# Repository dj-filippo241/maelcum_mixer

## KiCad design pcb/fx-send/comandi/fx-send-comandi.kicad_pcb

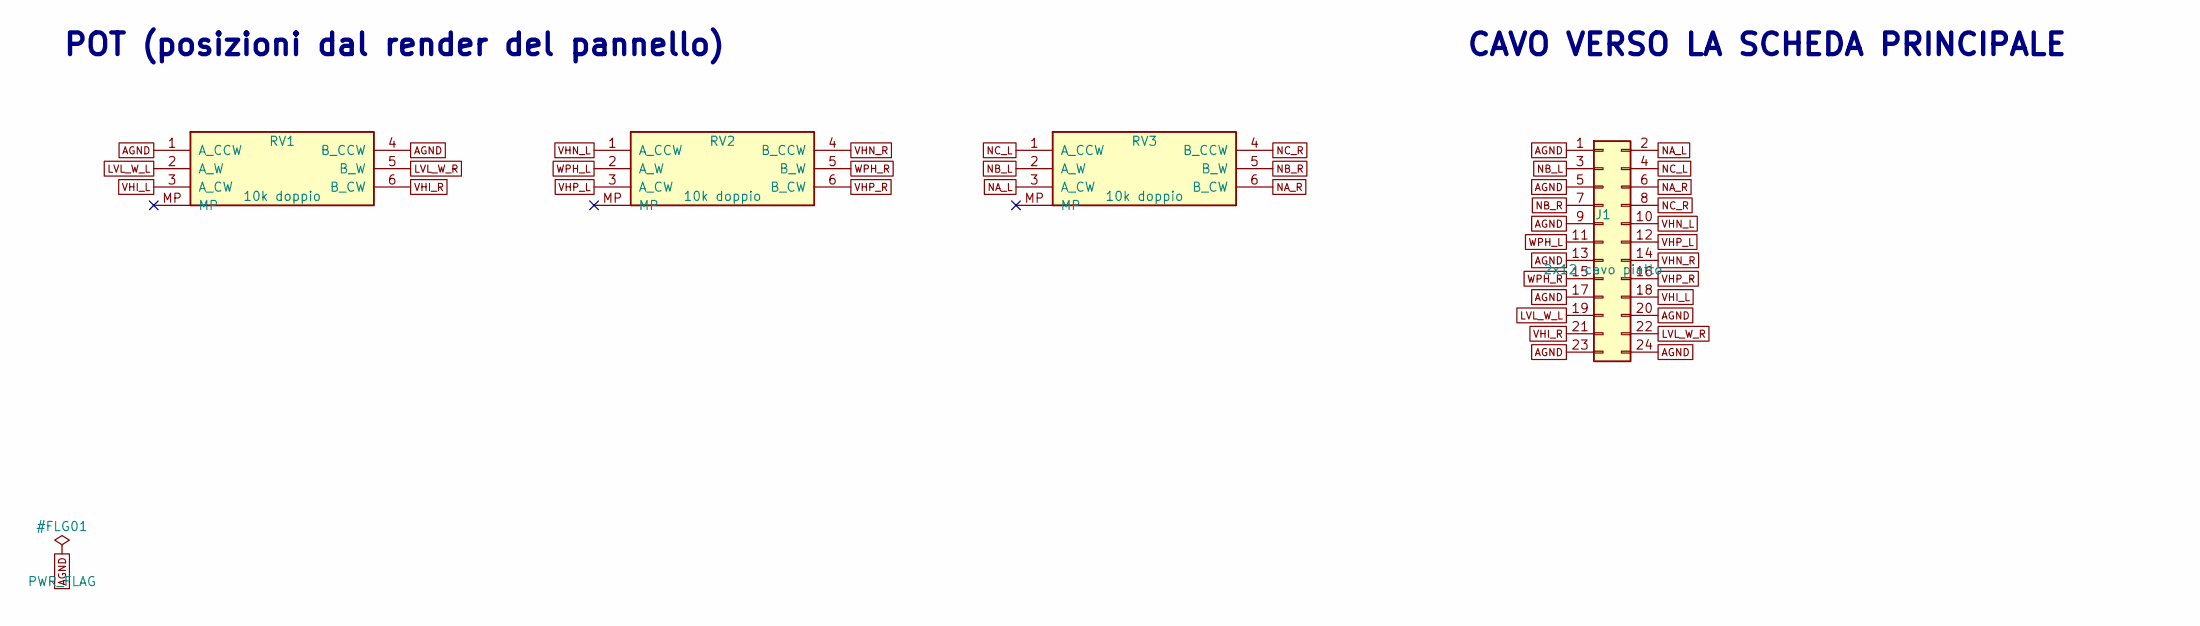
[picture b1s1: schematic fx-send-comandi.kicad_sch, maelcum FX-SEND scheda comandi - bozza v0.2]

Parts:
J1: 2x12 cavo piatto; PinHeader_2x12_P2.54mm_Vertical
RV1, RV2, RV3: 10k doppio; Potentiometer_Alps_RK09L_Double_Vertical

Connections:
AGND: J1.1, J1.5, J1.9, J1.13, J1.17, J1.20, J1.23, J1.24, RV1.1 (A_CCW), RV1.4 (B_CCW)
LVL_W_L: J1.19, RV1.2 (A_W)
LVL_W_R: J1.22, RV1.5 (B_W)
NA_L: J1.2, RV3.3 (A_CW)
NA_R: J1.6, RV3.6 (B_CW)
NB_L: J1.3, RV3.2 (A_W)
NB_R: J1.7, RV3.5 (B_W)
NC_L: J1.4, RV3.1 (A_CCW)
NC_R: J1.8, RV3.4 (B_CCW)
VHI_L: J1.18, RV1.3 (A_CW)
VHI_R: J1.21, RV1.6 (B_CW)
VHN_L: J1.10, RV2.1 (A_CCW)
VHN_R: J1.14, RV2.4 (B_CCW)
VHP_L: J1.12, RV2.3 (A_CW)
VHP_R: J1.16, RV2.6 (B_CW)
WPH_L: J1.11, RV2.2 (A_W)
WPH_R: J1.15, RV2.5 (B_W)

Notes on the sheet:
POT (posizioni dal render del pannello)
CAVO VERSO LA SCHEDA PRINCIPALE

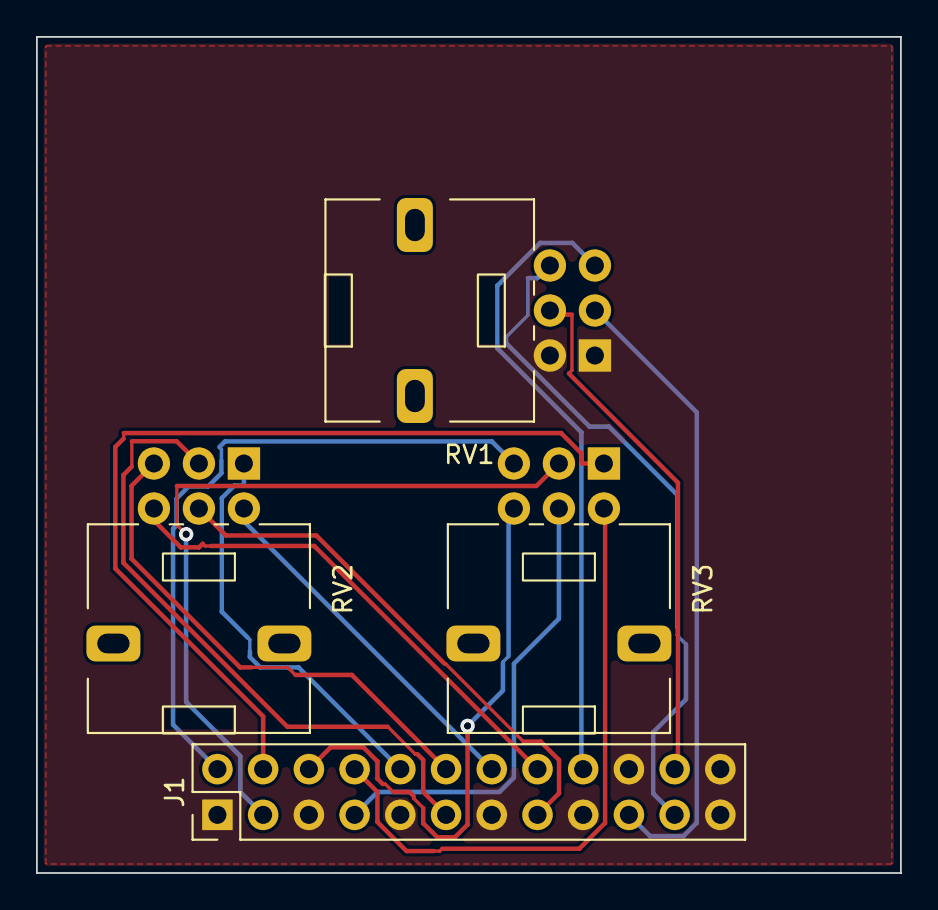
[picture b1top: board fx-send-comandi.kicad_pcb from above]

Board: 4 copper layers, 48.0 x 46.5 mm, 4 parts (0 on the bottom side), 17 nets.

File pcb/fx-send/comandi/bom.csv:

quantita;valore;impronta;riferimenti;nota
1;2x12 cavo piatto;PinHeader_2x12_P2.54mm_Vertical;J1;stesso ordine di J2 su fx-send.py
1;10k doppio;Potentiometer_Alps_RK09L_Double_Vertical;RV1;LEVEL: tutto antiorario = silenzio; manopola LEVEL, cappuccio 12.0 mm
1;10k doppio;Potentiometer_Alps_RK09L_Double_Vertical;RV2;HIGH: tutto antiorario = kill (Rp1h = 0, fx-eq2.cir); manopola EQ HIGH, cappuccio 6.0 mm
1;10k doppio;Potentiometer_Alps_RK09L_Double_Vertical;RV3;LOW Baxandall: tutto antiorario = kill (Za max), cursore = massa virtuale; manopola EQ LOW, cappuccio 6.0 mm

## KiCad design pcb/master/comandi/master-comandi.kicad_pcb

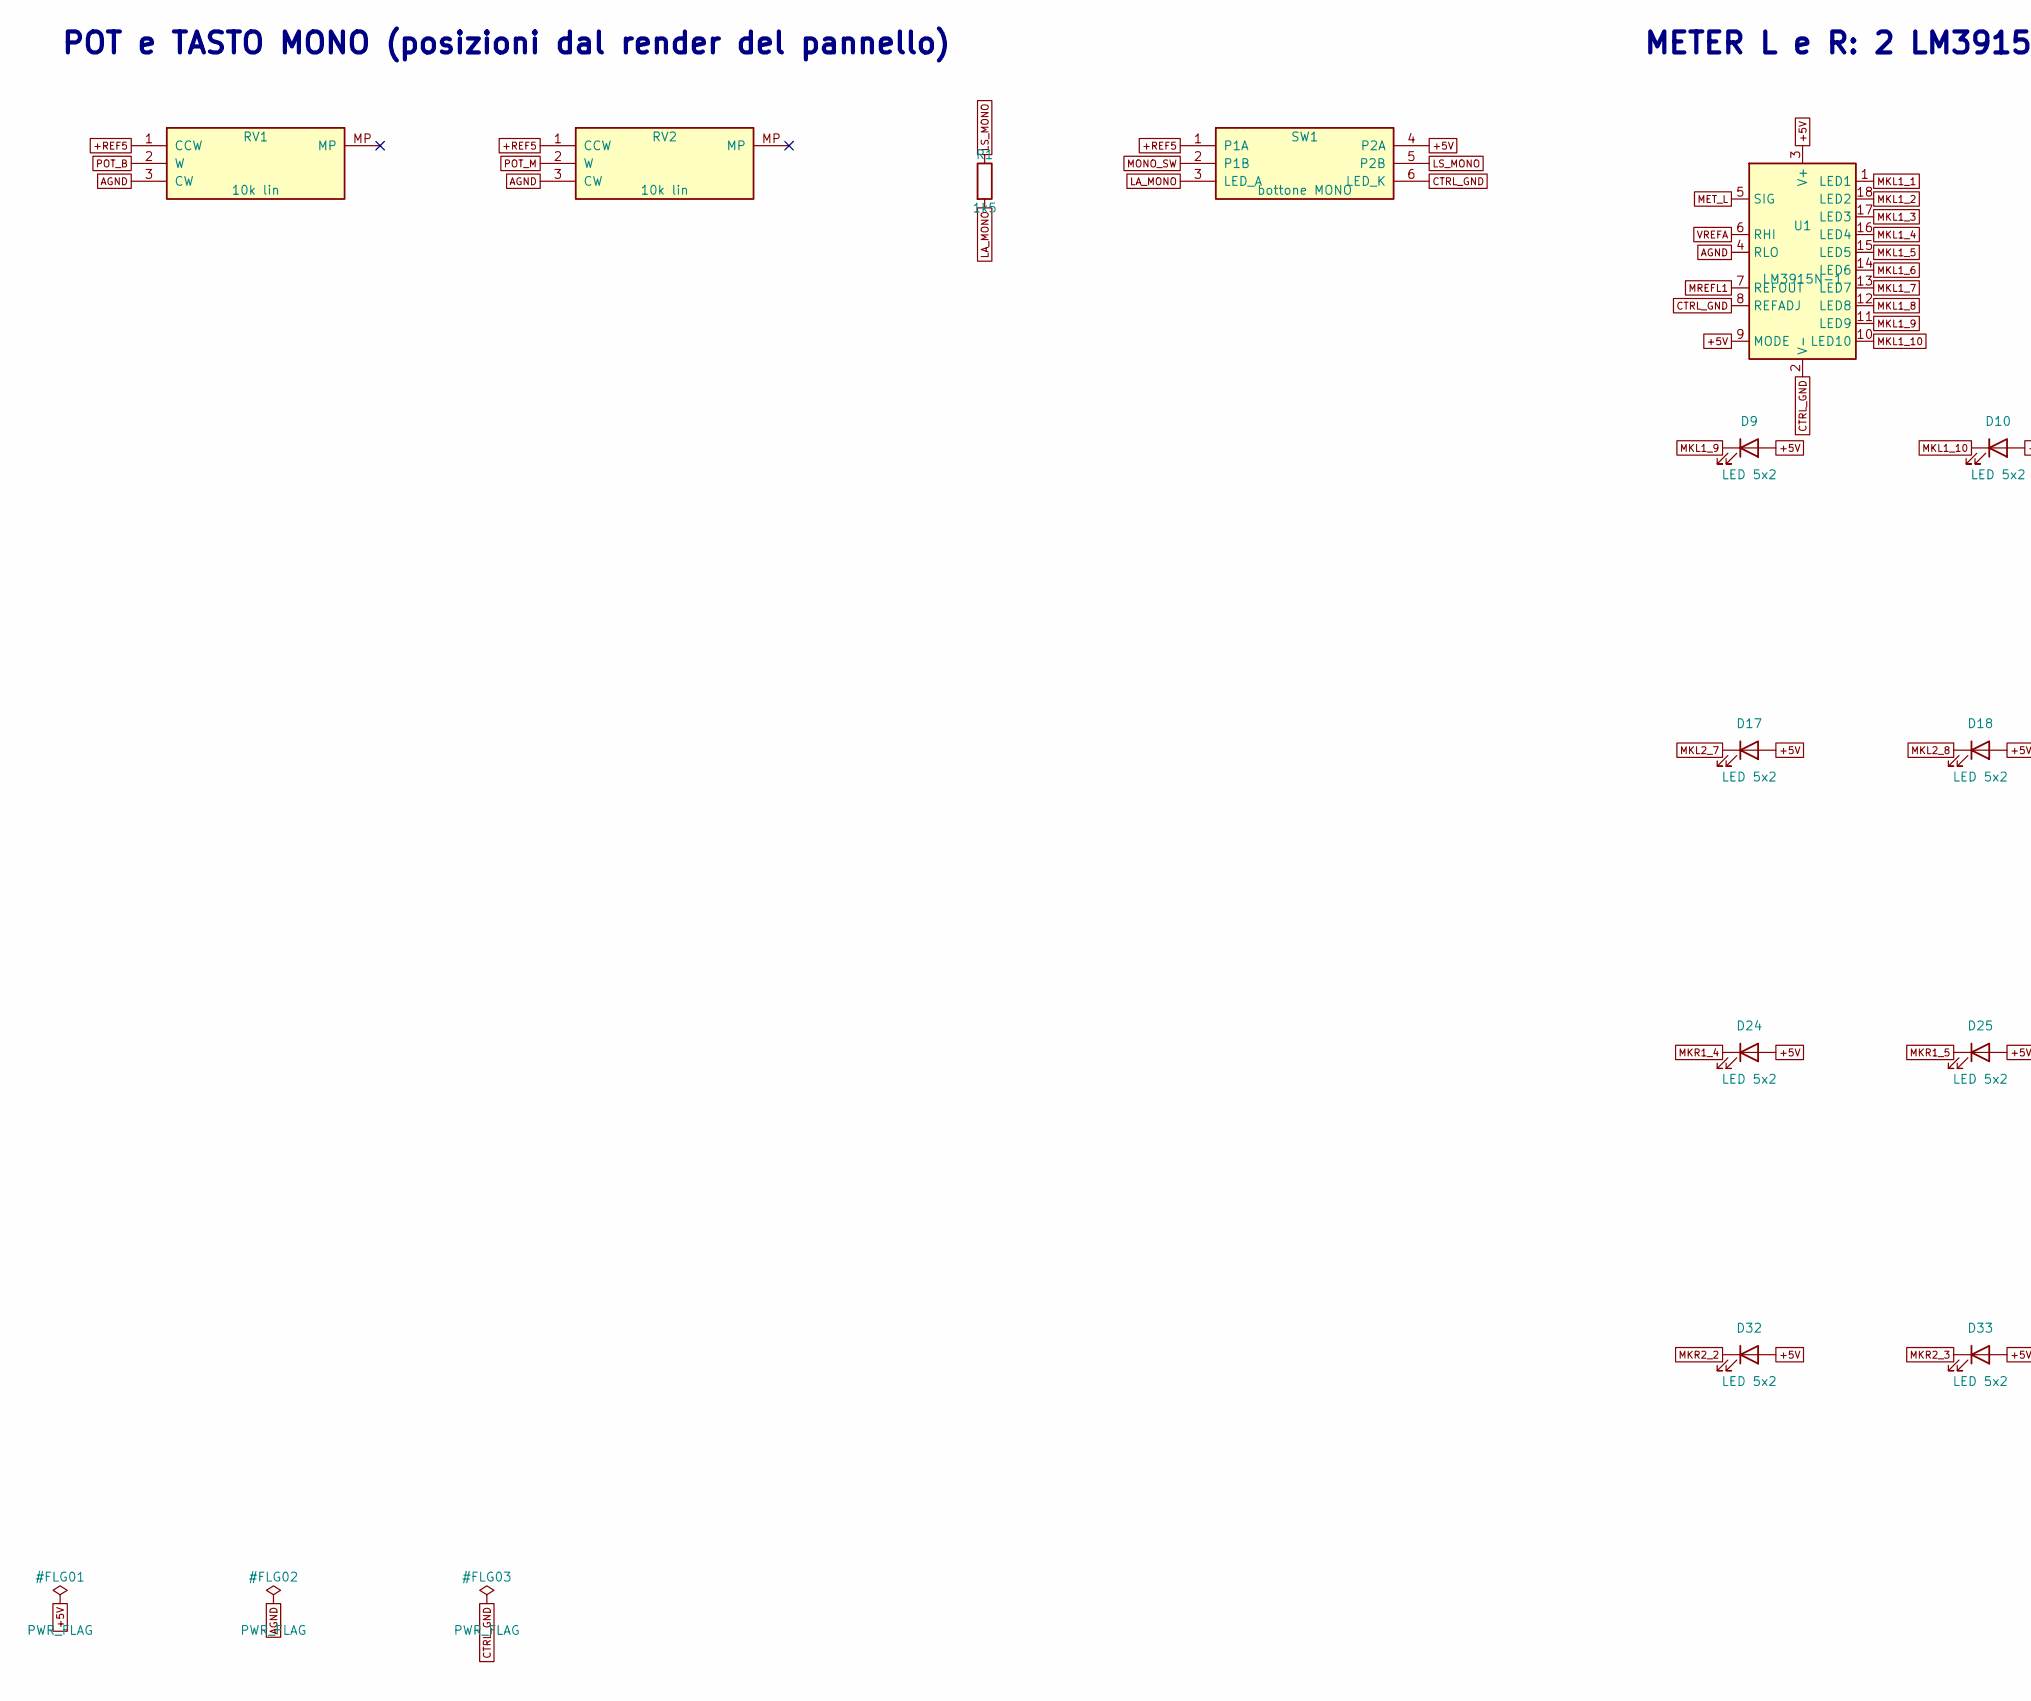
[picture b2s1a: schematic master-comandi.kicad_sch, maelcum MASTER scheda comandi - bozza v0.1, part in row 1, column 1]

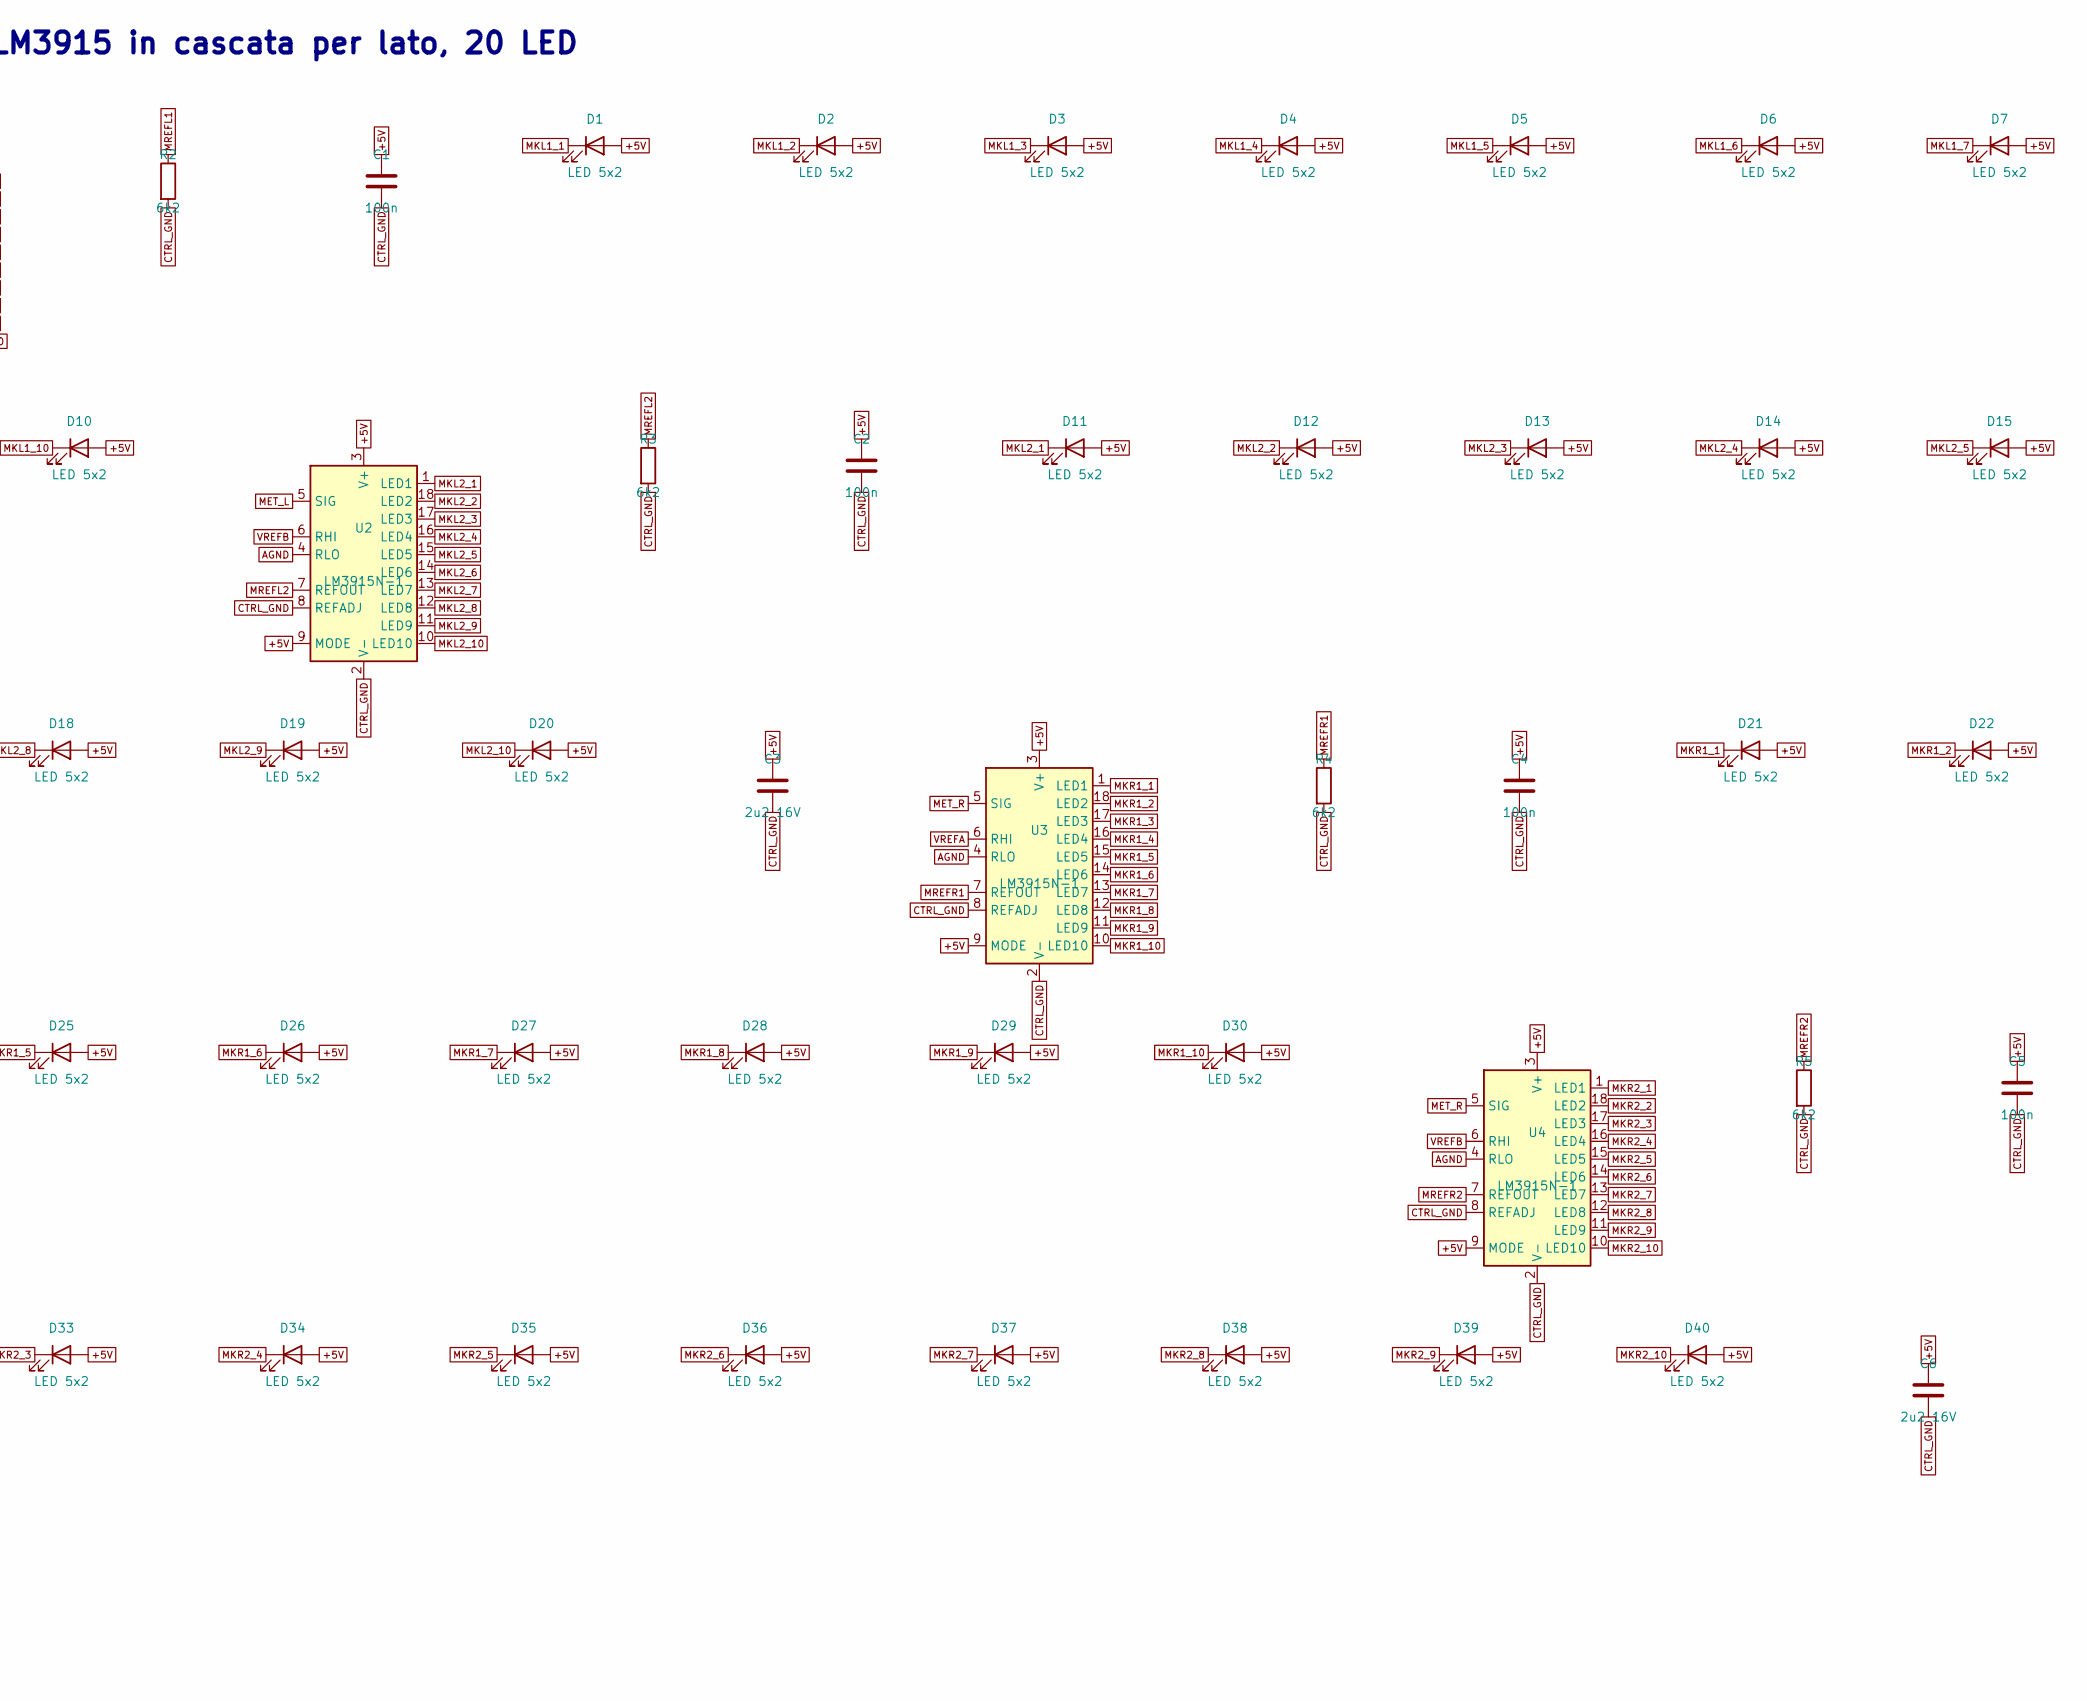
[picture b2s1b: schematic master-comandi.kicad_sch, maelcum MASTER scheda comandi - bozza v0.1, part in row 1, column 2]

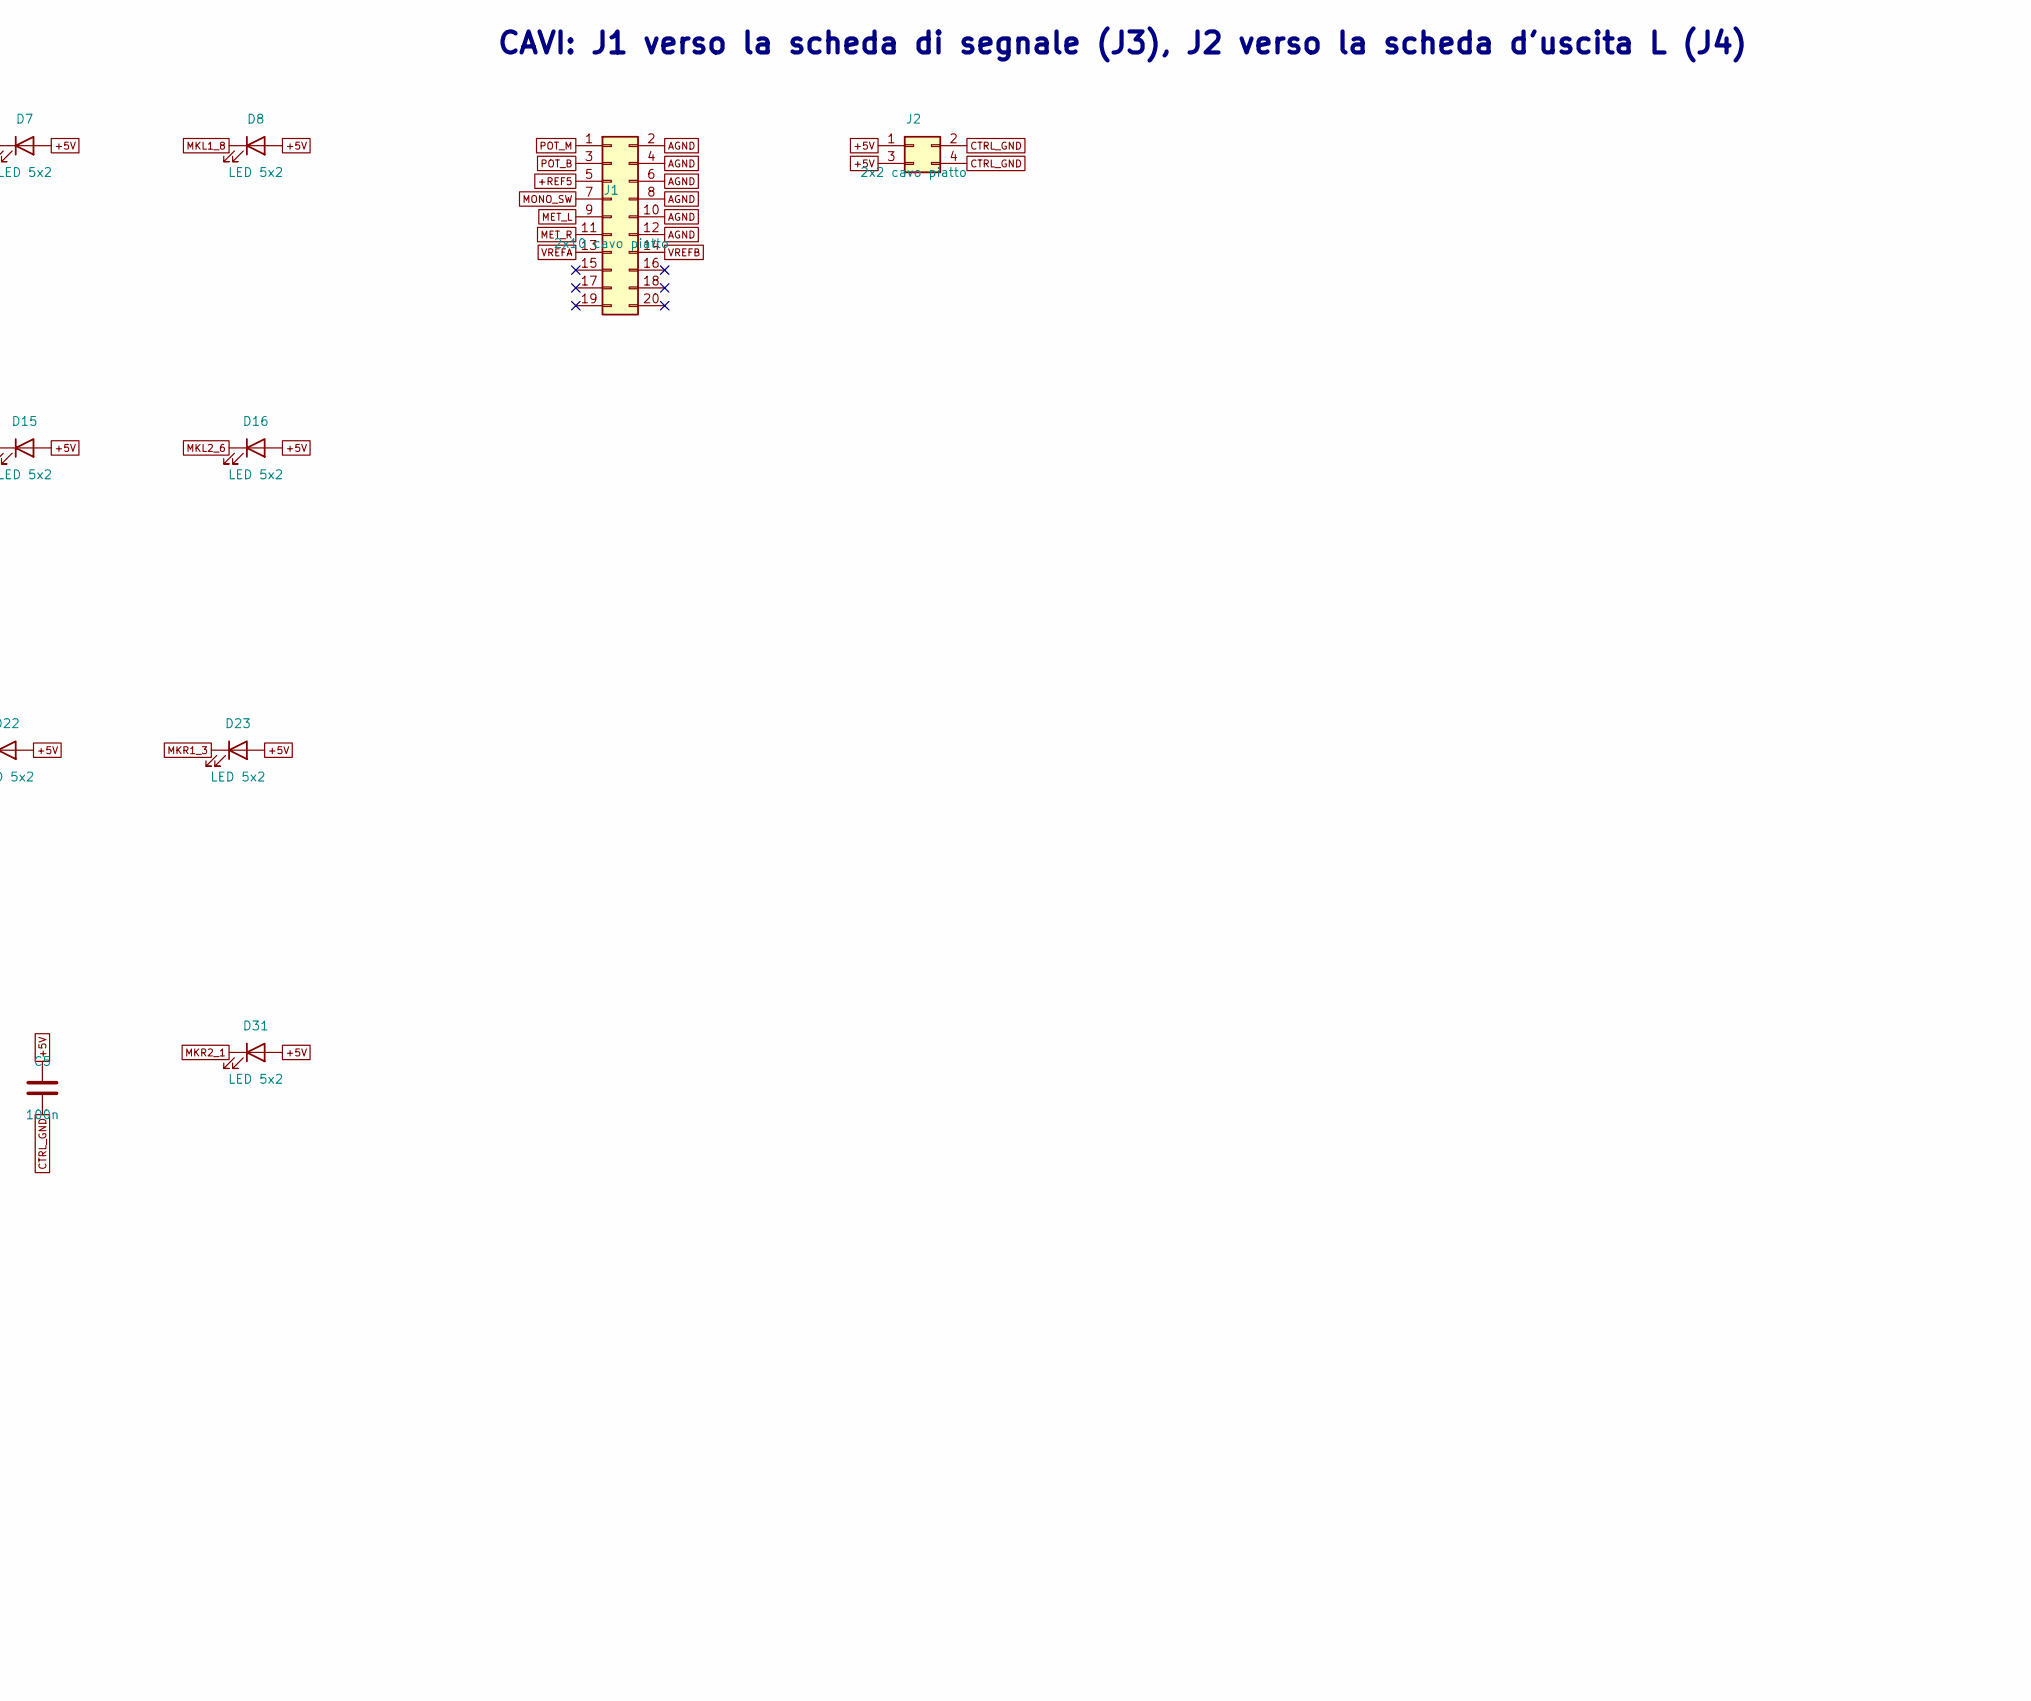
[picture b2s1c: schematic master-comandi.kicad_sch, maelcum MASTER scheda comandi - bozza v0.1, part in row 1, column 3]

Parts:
C1, C2, C4, C5: 100n; C_0805_2012Metric
C3, C6: 2u2 16V; C_1206_3216Metric
D1, D2, D3, D4, D5, D6, D7, D8, D9, D10, D11, D12, D13, D14, D15, D16, D17, D18, D19, D20, D21, D22, D23, D24, D25, D26, D27, D28, D29, D30, D31, D32, D33, D34, D35, D36, D37, D38, D39, D40: LED 5x2; LED_Rectangular_W5.0mm_H2.0mm
J1: 2x10 cavo piatto; PinHeader_2x10_P2.54mm_Vertical
J2: 2x2 cavo piatto; PinHeader_2x02_P2.54mm_Vertical
R1: 1k5; R_0805_2012Metric
R2, R3, R4, R5: 6k2; R_0805_2012Metric
RV1, RV2: 10k lin; Potentiometer_Alps_RK09L_Single_Vertical
SW1: bottone MONO; SW_NKK_GW12LJP
U1, U2, U3, U4: LM3915N-1; DIP-18_W7.62mm

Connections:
+5V: C1.1, C2.1, C3.1, C4.1, C5.1, C6.1, D1.2 (A), D2.2 (A), D3.2 (A), D4.2 (A), D5.2 (A), D6.2 (A), D7.2 (A), D8.2 (A), D9.2 (A), D10.2 (A), D11.2 (A), D12.2 (A), D13.2 (A), D14.2 (A), D15.2 (A), D16.2 (A), D17.2 (A), D18.2 (A), D19.2 (A), D20.2 (A), D21.2 (A), D22.2 (A), D23.2 (A), D24.2 (A), D25.2 (A), D26.2 (A), D27.2 (A), D28.2 (A), D29.2 (A), D30.2 (A), D31.2 (A), D32.2 (A), D33.2 (A), D34.2 (A), D35.2 (A), D36.2 (A), D37.2 (A), D38.2 (A), D39.2 (A), D40.2 (A), J2.1, J2.3, SW1.4 (P2A), U1.3 (V+), U1.9 (MODE), U2.3 (V+), U2.9 (MODE), U3.3 (V+), U3.9 (MODE), U4.3 (V+), U4.9 (MODE)
+REF5: J1.5, RV1.1 (CCW), RV2.1 (CCW), SW1.1 (P1A)
AGND: J1.2, J1.4, J1.6, J1.8, J1.10, J1.12, RV1.3 (CW), RV2.3 (CW), U1.4 (RLO), U2.4 (RLO), U3.4 (RLO), U4.4 (RLO)
CTRL_GND: C1.2, C2.2, C3.2, C4.2, C5.2, C6.2, J2.2, J2.4, R2.2, R3.2, R4.2, R5.2, SW1.6 (LED_K), U1.2 (V-), U1.8 (REFADJ), U2.2 (V-), U2.8 (REFADJ), U3.2 (V-), U3.8 (REFADJ), U4.2 (V-), U4.8 (REFADJ)
LA_MONO: R1.2, SW1.3 (LED_A)
LS_MONO: R1.1, SW1.5 (P2B)
MET_L: J1.9, U1.5 (SIG), U2.5 (SIG)
MET_R: J1.11, U3.5 (SIG), U4.5 (SIG)
MKL1_1: D1.1 (K), U1.1 (LED1)
MKL1_2: D2.1 (K), U1.18 (LED2)
MKL1_3: D3.1 (K), U1.17 (LED3)
MKL1_4: D4.1 (K), U1.16 (LED4)
MKL1_5: D5.1 (K), U1.15 (LED5)
MKL1_6: D6.1 (K), U1.14 (LED6)
MKL1_7: D7.1 (K), U1.13 (LED7)
MKL1_8: D8.1 (K), U1.12 (LED8)
MKL1_9: D9.1 (K), U1.11 (LED9)
MKL1_10: D10.1 (K), U1.10 (LED10)
MKL2_1: D11.1 (K), U2.1 (LED1)
MKL2_2: D12.1 (K), U2.18 (LED2)
MKL2_3: D13.1 (K), U2.17 (LED3)
MKL2_4: D14.1 (K), U2.16 (LED4)
MKL2_5: D15.1 (K), U2.15 (LED5)
MKL2_6: D16.1 (K), U2.14 (LED6)
MKL2_7: D17.1 (K), U2.13 (LED7)
MKL2_8: D18.1 (K), U2.12 (LED8)
MKL2_9: D19.1 (K), U2.11 (LED9)
MKL2_10: D20.1 (K), U2.10 (LED10)
MKR1_1: D21.1 (K), U3.1 (LED1)
MKR1_2: D22.1 (K), U3.18 (LED2)
MKR1_3: D23.1 (K), U3.17 (LED3)
MKR1_4: D24.1 (K), U3.16 (LED4)
MKR1_5: D25.1 (K), U3.15 (LED5)
MKR1_6: D26.1 (K), U3.14 (LED6)
MKR1_7: D27.1 (K), U3.13 (LED7)
MKR1_8: D28.1 (K), U3.12 (LED8)
MKR1_9: D29.1 (K), U3.11 (LED9)
MKR1_10: D30.1 (K), U3.10 (LED10)
MKR2_1: D31.1 (K), U4.1 (LED1)
MKR2_2: D32.1 (K), U4.18 (LED2)
MKR2_3: D33.1 (K), U4.17 (LED3)
MKR2_4: D34.1 (K), U4.16 (LED4)
MKR2_5: D35.1 (K), U4.15 (LED5)
MKR2_6: D36.1 (K), U4.14 (LED6)
MKR2_7: D37.1 (K), U4.13 (LED7)
MKR2_8: D38.1 (K), U4.12 (LED8)
MKR2_9: D39.1 (K), U4.11 (LED9)
MKR2_10: D40.1 (K), U4.10 (LED10)
MONO_SW: J1.7, SW1.2 (P1B)
MREFL1: R2.1, U1.7 (REFOUT)
MREFL2: R3.1, U2.7 (REFOUT)
MREFR1: R4.1, U3.7 (REFOUT)
MREFR2: R5.1, U4.7 (REFOUT)
POT_B: J1.3, RV1.2 (W)
POT_M: J1.1, RV2.2 (W)
VREFA: J1.13, U1.6 (RHI), U3.6 (RHI)
VREFB: J1.14, U2.6 (RHI), U4.6 (RHI)

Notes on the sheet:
POT e TASTO MONO (posizioni dal render del pannello)
METER L e R: 2 LM3915 in cascata per lato, 20 LED
CAVI: J1 verso la scheda di segnale (J3), J2 verso la scheda d'uscita L (J4)

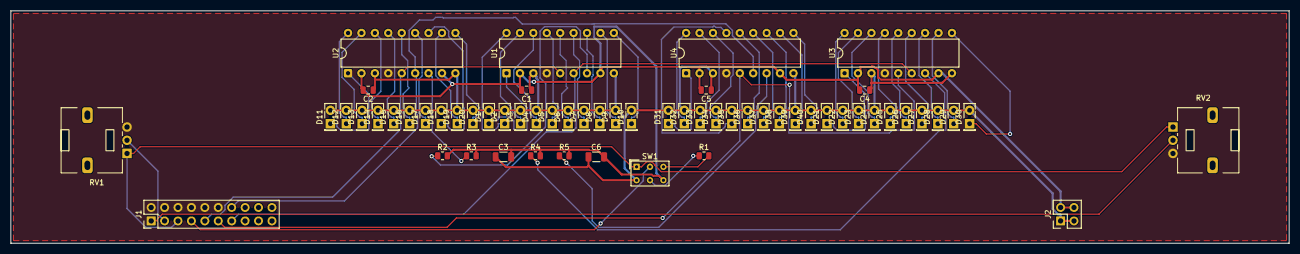
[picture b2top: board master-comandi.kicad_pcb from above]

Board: 4 copper layers, 242.0 x 44.0 mm, 60 parts (0 on the bottom side), 57 nets.

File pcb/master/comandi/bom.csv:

quantita;valore;impronta;riferimenti;nota
1;100n;C_0805_2012Metric;C1;disaccoppiamento dell'LM3915 L1
1;100n;C_0805_2012Metric;C2;disaccoppiamento dell'LM3915 L2
2;2u2 16V;C_1206_3216Metric;C3 C6;NOTA: riserva locale dei LED (cavo lungo)
1;100n;C_0805_2012Metric;C4;disaccoppiamento dell'LM3915 R1
1;100n;C_0805_2012Metric;C5;disaccoppiamento dell'LM3915 R2
1;LED 5x2;LED_Rectangular_W5.0mm_H2.0mm;D1;barra L, segmento 11 di 20 (1 = soglia più bassa); colore: metering §3
1;LED 5x2;LED_Rectangular_W5.0mm_H2.0mm;D10;barra L, segmento 20 di 20 (1 = soglia più bassa); colore: metering §3
1;LED 5x2;LED_Rectangular_W5.0mm_H2.0mm;D11;barra L, segmento 1 di 20 (1 = soglia più bassa); colore: metering §3
1;LED 5x2;LED_Rectangular_W5.0mm_H2.0mm;D12;barra L, segmento 2 di 20 (1 = soglia più bassa); colore: metering §3
1;LED 5x2;LED_Rectangular_W5.0mm_H2.0mm;D13;barra L, segmento 3 di 20 (1 = soglia più bassa); colore: metering §3
1;LED 5x2;LED_Rectangular_W5.0mm_H2.0mm;D14;barra L, segmento 4 di 20 (1 = soglia più bassa); colore: metering §3
1;LED 5x2;LED_Rectangular_W5.0mm_H2.0mm;D15;barra L, segmento 5 di 20 (1 = soglia più bassa); colore: metering §3
1;LED 5x2;LED_Rectangular_W5.0mm_H2.0mm;D16;barra L, segmento 6 di 20 (1 = soglia più bassa); colore: metering §3
1;LED 5x2;LED_Rectangular_W5.0mm_H2.0mm;D17;barra L, segmento 7 di 20 (1 = soglia più bassa); colore: metering §3
1;LED 5x2;LED_Rectangular_W5.0mm_H2.0mm;D18;barra L, segmento 8 di 20 (1 = soglia più bassa); colore: metering §3
1;LED 5x2;LED_Rectangular_W5.0mm_H2.0mm;D19;barra L, segmento 9 di 20 (1 = soglia più bassa); colore: metering §3
1;LED 5x2;LED_Rectangular_W5.0mm_H2.0mm;D2;barra L, segmento 12 di 20 (1 = soglia più bassa); colore: metering §3
1;LED 5x2;LED_Rectangular_W5.0mm_H2.0mm;D20;barra L, segmento 10 di 20 (1 = soglia più bassa); colore: metering §3
1;LED 5x2;LED_Rectangular_W5.0mm_H2.0mm;D21;barra R, segmento 11 di 20 (1 = soglia più bassa); colore: metering §3
1;LED 5x2;LED_Rectangular_W5.0mm_H2.0mm;D22;barra R, segmento 12 di 20 (1 = soglia più bassa); colore: metering §3
1;LED 5x2;LED_Rectangular_W5.0mm_H2.0mm;D23;barra R, segmento 13 di 20 (1 = soglia più bassa); colore: metering §3
1;LED 5x2;LED_Rectangular_W5.0mm_H2.0mm;D24;barra R, segmento 14 di 20 (1 = soglia più bassa); colore: metering §3
1;LED 5x2;LED_Rectangular_W5.0mm_H2.0mm;D25;barra R, segmento 15 di 20 (1 = soglia più bassa); colore: metering §3
1;LED 5x2;LED_Rectangular_W5.0mm_H2.0mm;D26;barra R, segmento 16 di 20 (1 = soglia più bassa); colore: metering §3
1;LED 5x2;LED_Rectangular_W5.0mm_H2.0mm;D27;barra R, segmento 17 di 20 (1 = soglia più bassa); colore: metering §3
1;LED 5x2;LED_Rectangular_W5.0mm_H2.0mm;D28;barra R, segmento 18 di 20 (1 = soglia più bassa); colore: metering §3
1;LED 5x2;LED_Rectangular_W5.0mm_H2.0mm;D29;barra R, segmento 19 di 20 (1 = soglia più bassa); colore: metering §3
1;LED 5x2;LED_Rectangular_W5.0mm_H2.0mm;D3;barra L, segmento 13 di 20 (1 = soglia più bassa); colore: metering §3
1;LED 5x2;LED_Rectangular_W5.0mm_H2.0mm;D30;barra R, segmento 20 di 20 (1 = soglia più bassa); colore: metering §3
1;LED 5x2;LED_Rectangular_W5.0mm_H2.0mm;D31;barra R, segmento 1 di 20 (1 = soglia più bassa); colore: metering §3
1;LED 5x2;LED_Rectangular_W5.0mm_H2.0mm;D32;barra R, segmento 2 di 20 (1 = soglia più bassa); colore: metering §3
1;LED 5x2;LED_Rectangular_W5.0mm_H2.0mm;D33;barra R, segmento 3 di 20 (1 = soglia più bassa); colore: metering §3
1;LED 5x2;LED_Rectangular_W5.0mm_H2.0mm;D34;barra R, segmento 4 di 20 (1 = soglia più bassa); colore: metering §3
1;LED 5x2;LED_Rectangular_W5.0mm_H2.0mm;D35;barra R, segmento 5 di 20 (1 = soglia più bassa); colore: metering §3
1;LED 5x2;LED_Rectangular_W5.0mm_H2.0mm;D36;barra R, segmento 6 di 20 (1 = soglia più bassa); colore: metering §3
1;LED 5x2;LED_Rectangular_W5.0mm_H2.0mm;D37;barra R, segmento 7 di 20 (1 = soglia più bassa); colore: metering §3
1;LED 5x2;LED_Rectangular_W5.0mm_H2.0mm;D38;barra R, segmento 8 di 20 (1 = soglia più bassa); colore: metering §3
1;LED 5x2;LED_Rectangular_W5.0mm_H2.0mm;D39;barra R, segmento 9 di 20 (1 = soglia più bassa); colore: metering §3
1;LED 5x2;LED_Rectangular_W5.0mm_H2.0mm;D4;barra L, segmento 14 di 20 (1 = soglia più bassa); colore: metering §3
1;LED 5x2;LED_Rectangular_W5.0mm_H2.0mm;D40;barra R, segmento 10 di 20 (1 = soglia più bassa); colore: metering §3
1;LED 5x2;LED_Rectangular_W5.0mm_H2.0mm;D5;barra L, segmento 15 di 20 (1 = soglia più bassa); colore: metering §3
1;LED 5x2;LED_Rectangular_W5.0mm_H2.0mm;D6;barra L, segmento 16 di 20 (1 = soglia più bassa); colore: metering §3
1;LED 5x2;LED_Rectangular_W5.0mm_H2.0mm;D7;barra L, segmento 17 di 20 (1 = soglia più bassa); colore: metering §3
1;LED 5x2;LED_Rectangular_W5.0mm_H2.0mm;D8;barra L, segmento 18 di 20 (1 = soglia più bassa); colore: metering §3
1;LED 5x2;LED_Rectangular_W5.0mm_H2.0mm;D9;barra L, segmento 19 di 20 (1 = soglia più bassa); colore: metering §3
1;2x10 cavo piatto;PinHeader_2x10_P2.54mm_Vertical;J1;stesso ordine di J3 su master-segnale.py; CLIP_L e CLIP_R liberi (nessun LED di clip sul pannello)
1;2x2 cavo piatto;PinHeader_2x02_P2.54mm_Vertical;J2;stesso ordine di J4 su master-uscita.py L: pin alternati (pcb/master/NOTE.md)
1;1k5;R_0805_2012Metric;R1;luce del bottone MONO dal secondo contatto
4;6k2;R_0805_2012Metric;R2 R3 R4 R5;NOTA: corrente dei LED ~2 mA (metering §1): I = 12,5 V / R, formula del datasheet LM3915 da verificare
1;10k lin;Potentiometer_Alps_RK09L_Single_Vertical;RV1;BOOTH: antiorario = silenzio; manopola rovescia: antiorario = +REF5; manopola BOOTH, pot di classe 14 mm, cappuccio 15.0 mm
1;10k lin;Potentiometer_Alps_RK09L_Single_Vertical;RV2;MASTER: antiorario = silenzio, scatto al centro = 0 dB, orario = +6 dB; manopola rovescia: antiorario = +REF5; manopola MASTER, pot di classe 14 mm, cappuccio 24.0 mm
1;bottone MONO;SW_NKK_GW12LJP;SW1;MONO: chiuso = mono (+REF5 su MONO_SW); luce ~2 mA dal secondo contatto; bottone MONO a ritenuta con luce; NOTA: impronta segnaposto (NKK GW12LJP)
1;LM3915N-1;DIP-18_W7.62mm;U1;barra L, 10 segmenti da 3 dB sotto VREFA; modo barra (MODE a V+); V- a CTRL_GND: le correnti dei LED restano fuori da AGND
1;LM3915N-1;DIP-18_W7.62mm;U2;barra L, 10 segmenti da 3 dB sotto VREFB; modo barra (MODE a V+); V- a CTRL_GND: le correnti dei LED restano fuori da AGND
1;LM3915N-1;DIP-18_W7.62mm;U3;barra R, 10 segmenti da 3 dB sotto VREFA; modo barra (MODE a V+); V- a CTRL_GND: le correnti dei LED restano fuori da AGND
1;LM3915N-1;DIP-18_W7.62mm;U4;barra R, 10 segmenti da 3 dB sotto VREFB; modo barra (MODE a V+); V- a CTRL_GND: le correnti dei LED restano fuori da AGND
